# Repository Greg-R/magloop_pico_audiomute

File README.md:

#  Printed circuit board design for the "Audio Mute" board for the Magnetic Loop Controller.

#  License

Please refer to the LICENSE file included in this repository.

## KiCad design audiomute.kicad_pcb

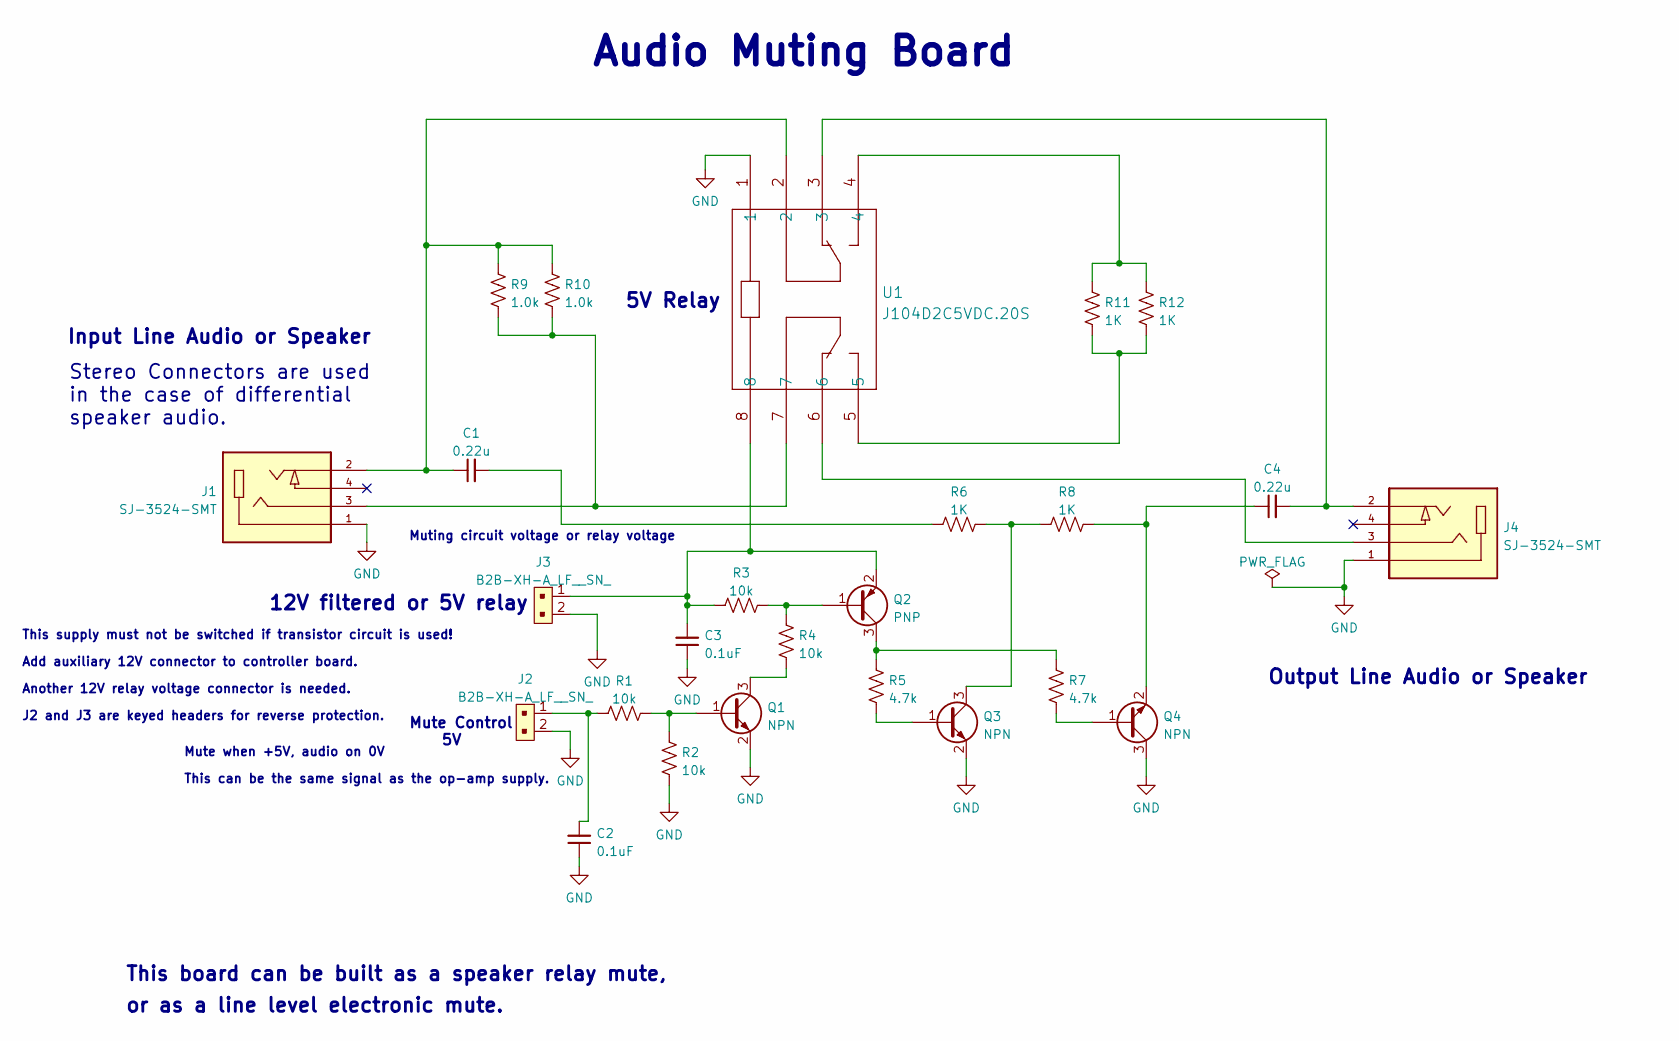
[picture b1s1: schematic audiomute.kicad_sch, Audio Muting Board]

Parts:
C1, C4: 0.22u; C_1206_3216Metric_Pad1.33x1.80mm_HandSolder
C2, C3: 0.1uF; C_1206_3216Metric_Pad1.33x1.80mm_HandSolder
J1, J4: SJ-3524-SMT; CUI_SJ-3524-SMT; PARTREV 1.03
J2, J3: B2B-XH-A_LF__SN_; PinHeader_1x2_P2.5mm_Drill1.1mm; MPN B2B-XH-A(LF)(SN); Digi-Key_PN 455-2247-ND
Q1, Q3, Q4: NPN; SOT-23
Q2: PNP; SOT-23
R1, R2, R3, R4: 10k; R_1206_3216Metric_Pad1.30x1.75mm_HandSolder
R5, R7: 4.7k; R_1206_3216Metric_Pad1.30x1.75mm_HandSolder
R6, R8, R11, R12: 1K; R_1206_3216Metric_Pad1.30x1.75mm_HandSolder
R9, R10: 1.0k; R_1206_3216Metric_Pad1.30x1.75mm_HandSolder
U1: J104D2C5VDC.20S

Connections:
GND: C2.1, C3.1, J1.1, J2.2, J3.2, J4.1, Q1.2 (E), Q3.2 (E), Q4.3 (C), R2.2, U1.1
unnamed: C1.1, J1.2, R9.1, R10.1, U1.2
unnamed: C1.2, R6.1
unnamed: C2.2, J2.1, R1.1
unnamed: C3.2, J3.1, Q2.2 (E), R3.1, U1.8
unnamed: C4.1, Q4.2 (E), R8.2
unnamed: C4.2, J4.2, U1.3
unnamed: J1.3, R9.2, R10.2, U1.7
unnamed: J4.3, U1.6
unnamed: Q1.1 (B), R1.2, R2.1
unnamed: Q1.3 (C), R4.2
unnamed: Q2.1 (B), R3.2, R4.1
unnamed: Q2.3 (C), R5.1, R7.1
unnamed: Q3.1 (B), R5.2
unnamed: Q3.3 (C), R6.2, R8.1
unnamed: Q4.1 (B), R7.2
unnamed: R11.2, R12.2, U1.4
unnamed: R11.1, R12.1, U1.5

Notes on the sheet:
Input Line Audio or Speaker
Mute when +5V, audio on 0V
Stereo Connectors are used in the case of differential speaker audio.
This supply must not be switched if transistor circuit is used!
Output Line Audio or Speaker
12V filtered or 5V relay
J2 and J3 are keyed headers for reverse protection.
Audio Muting Board
This board can be built as a speaker relay mute,
Mute Control 5V
Muting circuit voltage or relay voltage
or as a line level electronic mute.
Add auxiliary 12V connector to controller board.
Another 12V relay voltage connector is needed.
This can be the same signal as the op-amp supply.
5V Relay

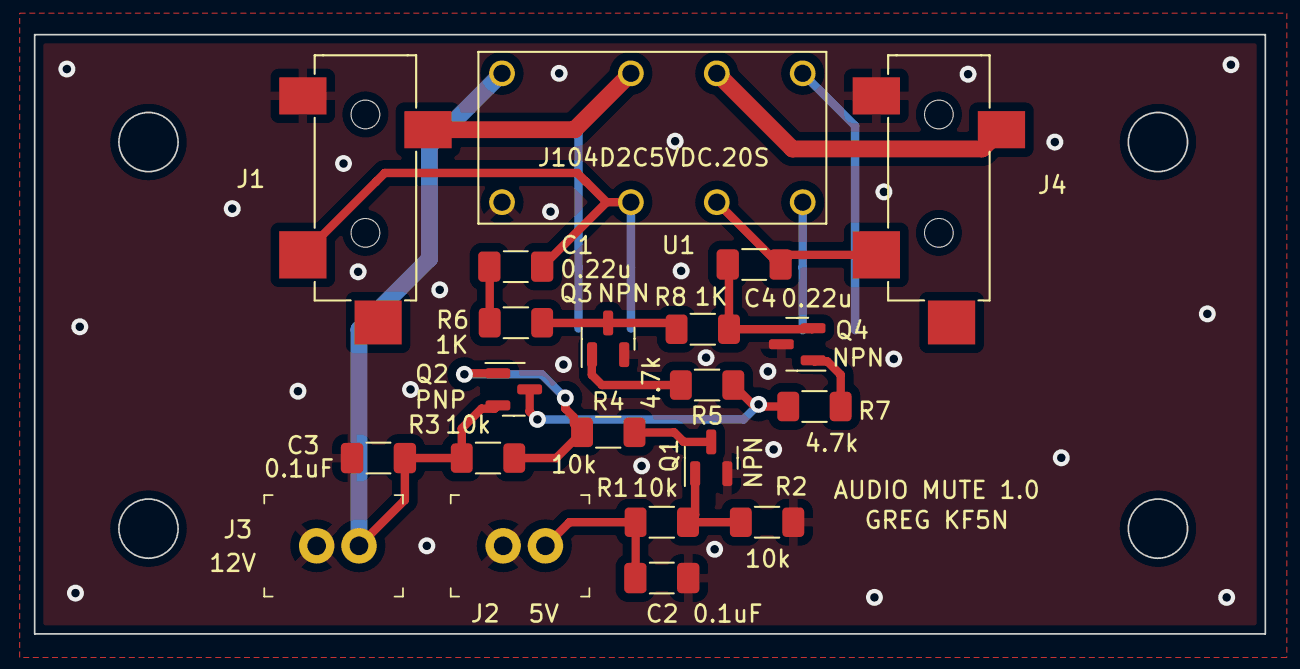
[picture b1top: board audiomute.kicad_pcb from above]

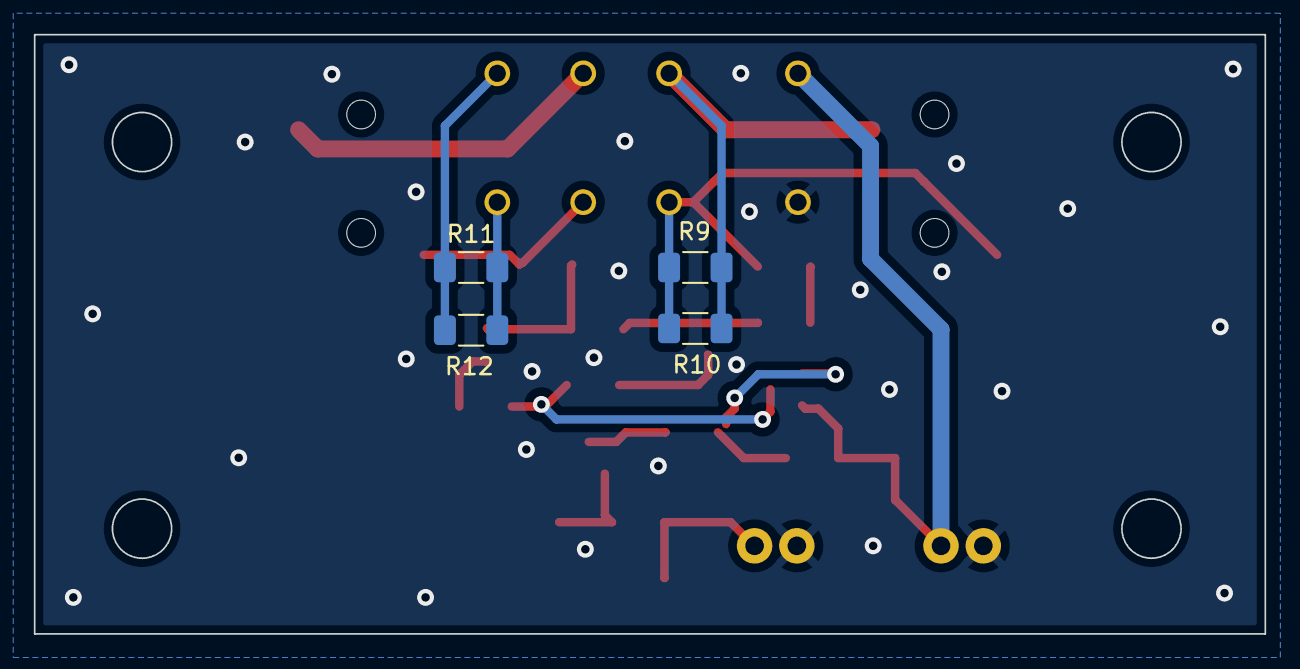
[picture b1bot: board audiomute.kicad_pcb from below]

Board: 2 copper layers, 72.8 x 35.4 mm, 25 parts (4 on the bottom side), 18 nets.

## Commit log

2022-05-17 Initial commit.
2022-05-17 Added LICENSE file.
2022-05-28 Minor updates to layout and created new gerbers and drills.
2022-08-15 Updated schematic with stereo connectors to allow differential speaker.
2022-08-16 Replaced relay with different part due to cost. Moved coupling capacitors. Revised notes to remove ambiguity.
2022-08-16 Minor update to notes in schematic.
2022-11-10 Finished version 1.0. Ready to release PCB.
2022-11-29 Revised board uses larger relay, and has differential input and output.

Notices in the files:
parts and their libraries:
Copyright 2021 Accelerated Designs. All rights reserved.
